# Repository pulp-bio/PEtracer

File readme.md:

# PEtra: A Flexible and Open-Source PE Loop Tracer

## Overview
PEtra is an open source, versatile polarisation electric field (PE) loop tracer designed to accurately characterise the ferroelectric properties of polymeric piezoelectrics. It has been developed to overcome the limitations of traditional charge measurement techniques such as the Sawyer tower circuit, particularly for screen-printed poly(vinylidene fluoride-tetrafluoroethylene) (P(VDF-TrFE)) transducers.
PEtra achieves sensitivity as low as 2 pA and supports a wide frequency range, making it ideal for optimising the performance of flexible and wearable ultrasound transducers.

> *IMPORTANT NOTE:* This document describes the setup and measurement functions of PEtra. We do not cover the methods or equipment required to generate the bipolar (e.g. sinusoidal) inputs needed to load the transducer for characterisation.

## Features
- **Ultra-Low Current Sensitivity:** Measures currents down to 2 pA.
- **Adjustable Gain Settings:** Transimpedance gains from 10³ V/A to 10⁷ V/A.
- **Wide Frequency Range:** 0.1 Hz to 200 Hz for most gain settings.
- **Open-Source Design:** Fully documented hardware available on [GitHub](https://github.com/pulp-bio/PEtracer).
- **Suitable for Polymer Piezoelectric:** Optimized for screen-printed P(VDF-TrFE) transducers with slow switching times.

## Applications
- Characterizing PE loops in ferroelectric polymers.
- Optimizing fabrication processes for screen-printed P(VDF-TrFE) devices.
- Research on flexible and wearable ultrasound transducers.

## Hardware Components
1. **Transimpedance Amplifier (TIA):** LMP7721 (Texas Instruments) op-amp with ultra-low input bias current of 3 fA.
2. **Selectable Gain Network:** DIP switch for adjusting feedback resistors and capacitors.
3. **Input Protection Circuit:** Fuse and clipping diodes to safeguard the TIA.
4. **Power Supply:** Low-dropout regulator (LDO) providing a stable ±2.5V supply.
5. **Interaction Points:**
   - **Transducer In:** Current input and virtual ground.
   - **Voltage Supply:** Power input.
   - **Gain Switch:** Gain selection via DIP switch.
   - **Oscilloscope Out:** Signal output for measurement.

## Setup Instructions
### 1. Assemble the Hardware
Refer to the schematics and PCB layout available in the [GitHub repository](https://github.com/pulp-bio/PEtracer). Ensure all components are soldered correctly and check for proper connections.

### 2. Connecting the transducer
1. Connect one electrode of your transducer to the excitation voltage supply:
   - Make sure that this circuit is isolated from earth. 
   - If necessary, take into account the direction of polarisation of the transducer.
2. Connect the second electrode of the transducer to the **Transducer In** terminal on PEtra.

### 3. Power-up PEtra
1. Connect a stable ±2.5V power supply to the **Voltage Supply** terminal.
2. Verify the power LEDs light up to confirm correct operation.

### 4. Adjust Gain Settings
Use the DIP switch to select the desired transimpedance gain based on the expected current range:
- 10³ V/A to 10⁷ V/A (decade steps).

### 5. Output Signal Measurement
1. Connect the **Oscilloscope Out** terminal to an oscilloscope of your choice.
2. Measure the output voltage corresponding to the amplified current.

## Example Usage

### Measuring a PE Loop
1. Set up the transducer as per the instructions above.
2. Apply a sinusoidal voltage to the transducer.
3. Observe the PE loop by plotting the output signal from PEtra.

### Optimizing Transducer Design
1. Measure the hysteresis characteristics (e.g., remnant polarization, coercive field).
2. Adjust the fabrication process based on the observed PE loops.

## Repository Structure
- `./hw` - Schematics and PCB layouts.
- `./data` - PEtra image data.

## Contributors

PEtra was developed at the [Integrated Systems Laboratory (IIS)](https://iis.ee.ethz.ch/) at ETH Zurich by:
- [Marc-André Wessner](https://www.linkedin.com/in/marcandre-wessner/) (Hardware Design, Simulation and Characterization)
- [Federico Villani](https://scholar.google.com/citations?hl=en&user=5LgLMCEAAAAJ) (Hardware Verification, Characterization and Validation)
- [Christoph Leitner](https://scholar.google.com/citations?user=_gUK_isAAAAJ&hl=en) (Conceptualization, Methodology and Supervision)

Thanks to all the people who contributed to the PEtra platform: [Luca Benini](https://scholar.google.com/citations?user=8riq3sYAAAAJ&hl=en&oi=ao), [Francesco Greco](https://scholar.google.com/citations?hl=en&user=-YzZbl8AAAAJ), [Kirill Keller](https://scholar.google.com/citations?hl=en&user=LKh_eWoAAAAJ), [Sofia Papa](https://www.linkedin.com/in/sofia-papa-a442a7188/),  [Laura M. Ferrari](https://scholar.google.com/citations?user=vNBGL2kAAAAJ&hl=en&oi=ao)

## Citation
If you would like to reference the project, please cite the following [paper](https://ieeexplore.ieee.org/abstract/document/10793576):

```
@inproceedings{wessner2024petra,
  author={Wessner, Marc-Andre and Villani, Federico and Papa, Sofia and Keller, Kirill and Ferrari, Laura and Greco, Francesco and Benini, Luca and Leitner, Christoph},
  booktitle={2024 IEEE Ultrasonics, Ferroelectrics, and Frequency Control Joint Symposium (UFFC-JS)}, 
  title={PEtra: A Flexible and Open-Source PE Loop Tracer for Polymer Thin-Film Transducers}, 
  year={2024},
  pages={1-4},
  doi={10.1109/UFFC-JS60046.2024.10793576}}
```

## License
This repository is released under Solderpad v0.51 (`SHL-0.51`). For details see `./LICENSE.hw`. Files in the `./data` directory are released under Creative Commons Attribution 4.0 International License (`CC-BY-4.0`); refer to `./LICENSE.data` for more information.

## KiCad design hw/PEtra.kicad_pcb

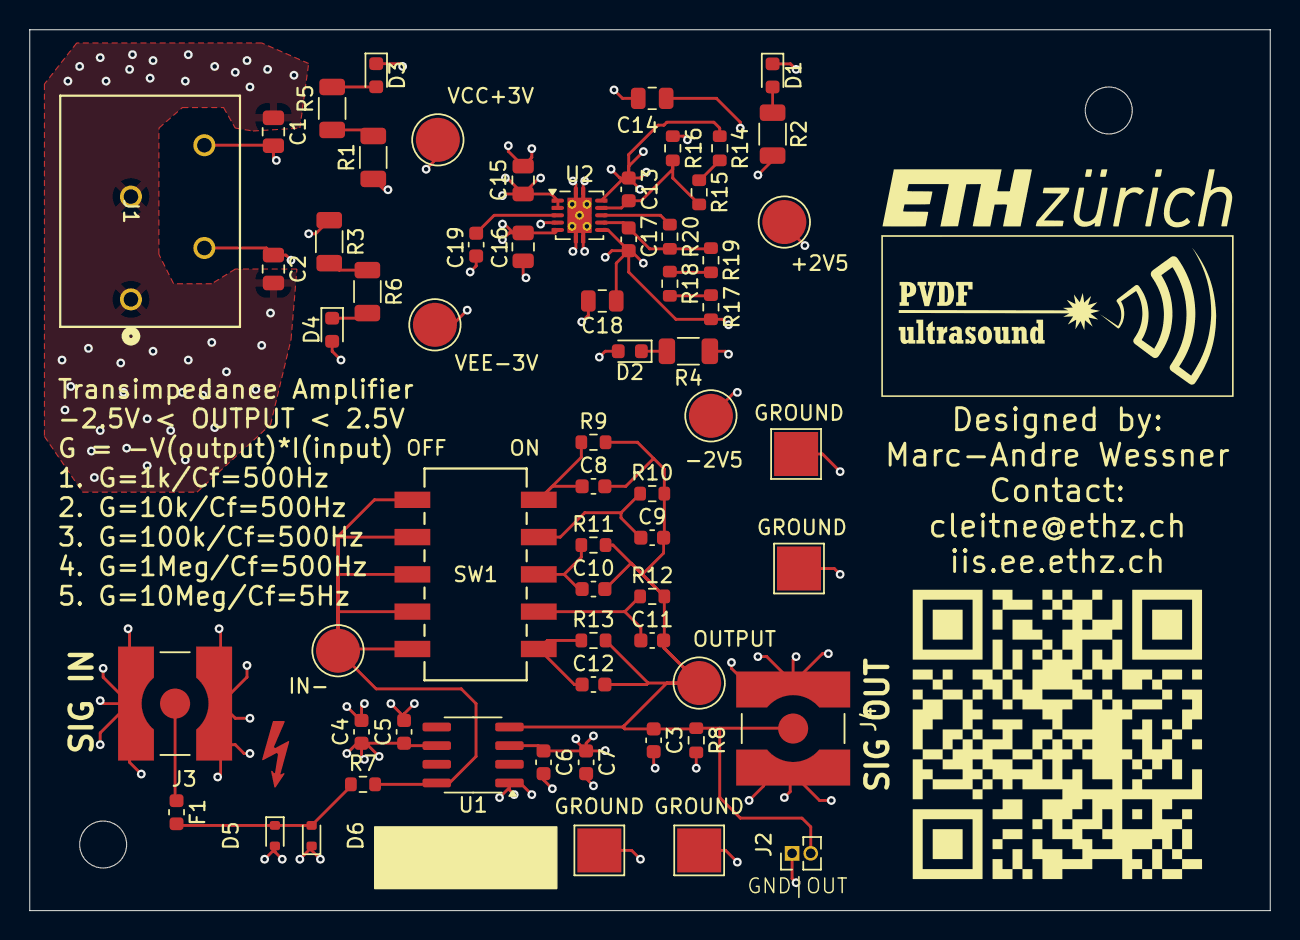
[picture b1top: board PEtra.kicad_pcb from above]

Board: 4 copper layers, 84.5 x 60.0 mm, 63 parts (0 on the bottom side), 27 nets.

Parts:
+2V5: +2V5; TestPoint_Pad_D3.0mm
-2V5: -2V5; TestPoint_Pad_D3.0mm
C1, C2, C14, C15, C16, C18: 10uF; C_0805_2012Metric
C3, C5, C6: 1nF; C_0603_1608Metric
C4, C7, C8: 300nF; C_0603_1608Metric
C9: 30nF; C_0603_1608Metric
C10, C12: 3nF; C_0603_1608Metric
C11: 0.3nF; C_0603_1608Metric
C13, C17, C19: 10nF; C_0603_1608Metric
D1, D3: GREEN; LED_0603_1608Metric
D2, D4: RED; LED_0603_1608Metric
D5, D6: BAS716; D_SOD-523
F1: Fuse_Small; Fuse_0603_1608Metric
GROUND: GNDTP; TestPoint_Pad_3.0x3.0mm
GROUND#2, GROUND#3: GNDTP; TestPoint_Pad_3.0x3.0mm
GROUND#4: GROUNDTP; TestPoint_Pad_3.0x3.0mm
IN-: IN-; TestPoint_Pad_D3.0mm
J1: Conn_01x04_Socket; CONN_1985218
J2: Conn_01x02_Pin; PinHeader_1x02_P1.27mm_Vertical
J3, J4: Conn_Coaxial; LINX_CONREVSMA001-SMD-G
OUTPUT: Output; TestPoint_Pad_D3.0mm
R1, R2, R3, R4, R5, R6: 25; R_1206_3216Metric
R7: 0.1; R_0603_1608Metric
R8, R10, R15, R16, R18, R19, R20: 10k; R_0603_1608Metric
R9, R14, R17: 1k; R_0603_1608Metric
R11: 100k; R_0603_1608Metric
R12: 1Meg; R_0603_1608Metric
R13: 10Meg; R_0603_1608Metric
SW1: SW_DIP_x05; SW5_219SMT
U1: LMP7721MA/NOPB; SOIC-8_3.9x4.9mm_P1.27mm
U2: TPS7A39; Texas_S-PVSON-N10_ThermalVias
VCC+3V: VCC; TestPoint_Pad_D3.0mm
VEE-3V: VEE; TestPoint_Pad_D3.0mm

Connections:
+2V5: +2V5.1, C4.1, C5.1, C13.1, C14.1, R2.1, R14.1, U1.6 (V+), U2.10 (OUTP)
-2V5: -2V5.1, C6.1, C7.1, C17.1, C18.1, R4.1, R17.2, U1.3 (V-), U2.6 (OUTN)
/Feedback Network/GAIN_MODE1: C8.1, R9.1, SW1.10
/Feedback Network/GAIN_MODE2: C9.1, R10.1, SW1.9
/Feedback Network/GAIN_MODE3: C10.1, R11.1, SW1.8
/Feedback Network/GAIN_MODE4: C11.1, R12.1, SW1.7
/Feedback Network/GAIN_MODE5: C12.1, R13.1, SW1.6
/IN-: IN-.1, R7.2, SW1.1, SW1.2, SW1.3, SW1.4, SW1.5, U1.8 (IN-)
/Output: C3.1, C8.2, C9.2, C10.2, C11.2, C12.2, J2.2, J4.1 (In), OUTPUT.1, R8.1, R9.2, R10.2, R11.2, R12.2, R13.2, U1.4 (OUT)
/Power LDO/BUF: R20.1, U2.8 (BUF)
/Power LDO/FBN: C17.2, R19.2, R20.2, U2.7 (FBN)
/Power LDO/FBP: C13.2, R15.1, R16.2, U2.9 (FBP)
GND: C1.1, C2.2, C3.2, C4.2, C5.2, C6.2, C7.2, C14.2, C15.2, C16.2, C18.2, C19.2, D1.1 (K), D2.2 (A), D3.1 (K), D4.2 (A), D5.2 (A), D6.1 (K), GROUND.1, GROUND#2.1, GROUND#3.1, GROUND#4.1, J1.1, J1.3, J2.1, J3.2 (Ext), J4.2 (Ext), R8.2, R16.1, U1.1 (IN+), U2.4 (GND), U2.11 (GND)
unnamed: D1.2 (A), R2.2
unnamed: D2.1 (K), R4.2
unnamed: D3.2 (A), R5.2
unnamed: D4.1 (K), R6.2
unnamed: D5.1 (K), D6.2 (A), F1.2, R7.1
unnamed: F1.1, J3.1 (In)
unnamed: R1.2, R5.1
unnamed: R3.2, R6.1
unnamed: R14.2, R15.2
unnamed: R17.1, R18.1
unnamed: R18.2, R19.1
unnamed: C19.1, U2.3 (NR/SS)
VCC: C1.2, C15.1, J1.4, R1.1, U2.1 (INP), U2.2 (EN), VCC+3V.1
VEE: C2.1, C16.1, J1.2, R3.1, U2.5 (INN), VEE-3V.1

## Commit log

2025-01-29 PEtra IUS 2024 - Initial Commit

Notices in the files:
parts and their libraries:
LICENSE: SOLDERPAD HARDWARE LICENSE version 0.51
